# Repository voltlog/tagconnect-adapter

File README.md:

# TagConnect to ST-Link/J-Link JTAG Adapter PCB
I designed this adapter PCB to alow easy connection of the standard TC2030 or TC2050 TagConnect series programming cables to the popular programming/debugging tools like the ST-Link or J-Link which feature a different connector.

Additionally a 6-pin VoltLink connector™ has been added so that a standard TC2030 footprint on a PCB can be used to interface to the VoltLink USB to serial adapter.

If you would like to order one of these adapters ready assembled, check out my [Tindie store](https://voltlog.com/y/tagco).

More info about this project in [Voltlog #460](https://youtu.be/9-e_gcYaEM0).

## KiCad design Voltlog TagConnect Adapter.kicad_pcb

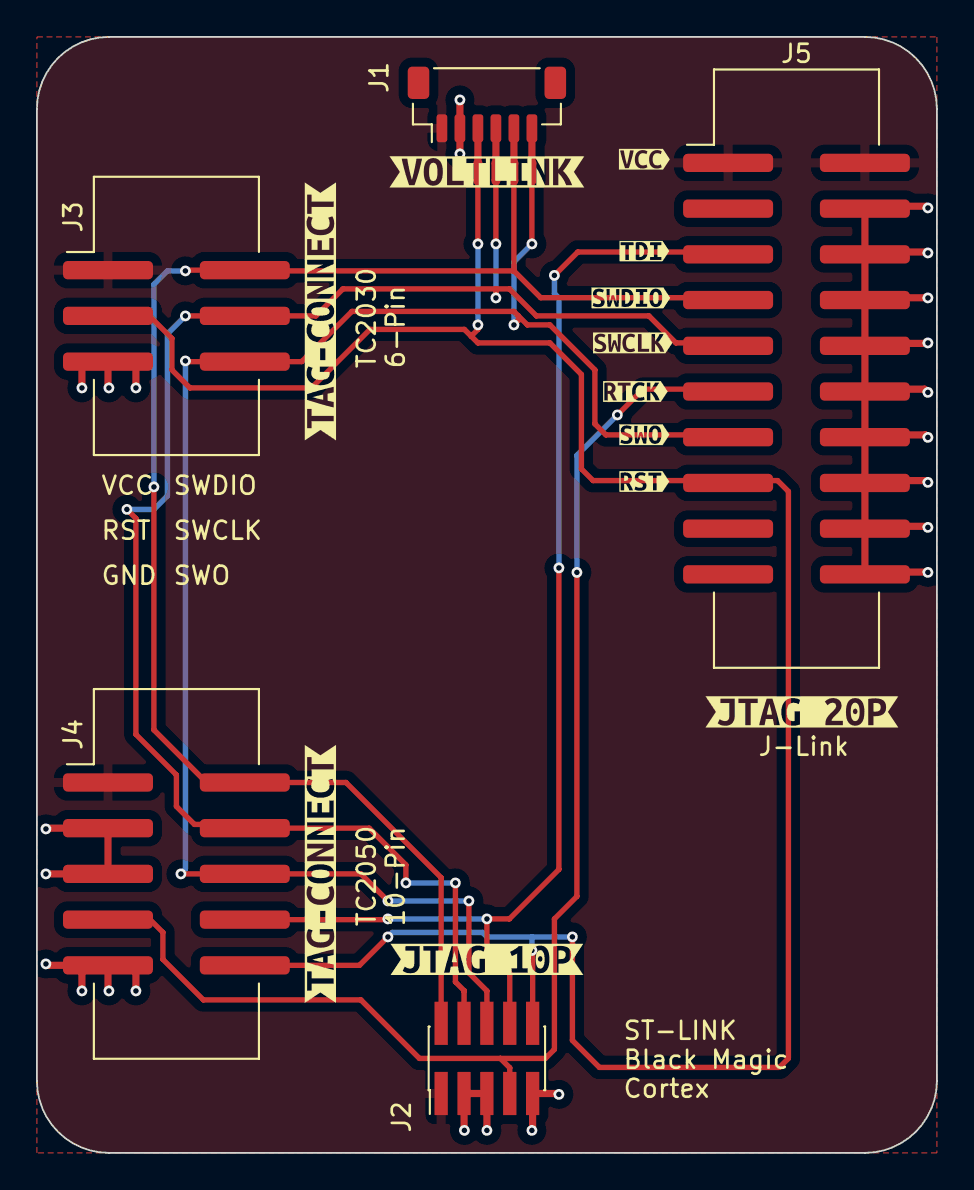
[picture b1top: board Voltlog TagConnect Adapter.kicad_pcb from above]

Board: 2 copper layers, 50.0 x 62.0 mm, 22 parts (0 on the bottom side), 12 nets.

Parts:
J1: VoltLink_target; VoltLink-vertical
J2: JTAG 10pin P1.27mm; PinHeader_2x05_P1.27mm_Vertical_SMD
J3: TC2030-IDC 6-Pin; IDC-Header_2x03_P2.54mm_Vertical_SMD
J4: TC2050-IDC 10-Pin; IDC-Header_2x05_P2.54mm_Vertical_SMD
J5: Conn_ARM_JTAG_SWD_20; IDC-Header_2x10_P2.54mm_Vertical_SMD
NT1, NT2, NT3, NT4: NetTie_2; NetTie-2_SMD_Pad0.5mm
V1: VOLTLOG_LOGO; voltlog_mask_3mm
kibuzzard-64FC233E: G***; kibuzzard-64FC233E
kibuzzard-64FC234D: G***; kibuzzard-64FC234D
kibuzzard-64FC235A: G***; kibuzzard-64FC235A
kibuzzard-64FC2381: G***; kibuzzard-64FC2381
kibuzzard-64FC2395: G***; kibuzzard-64FC2395
kibuzzard-6507D7D7: G***; kibuzzard-6507D7D7
kibuzzard-6507D7E8: G***; kibuzzard-6507D7E8
kibuzzard-6507D7FA: G***; kibuzzard-6507D7FA
kibuzzard-6507D800: G***; kibuzzard-6507D800
kibuzzard-6507D807: G***; kibuzzard-6507D807
kibuzzard-6507D812: G***; kibuzzard-6507D812
kibuzzard-6507D818: G***; kibuzzard-6507D818

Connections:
/EN: J1.6 (EN), NT4.1
/IO0: J1.5 (IO0), NT3.1
/RESET: J2.10, J3.3, J4.10, J5.15 (~SRST), NT1.2
/RTCK: J2.7, J4.7, J5.11 (RTCK)
/RXD: J1.4 (RXD), NT2.1
/TCLK/SWCLK: J2.4, J3.4, J4.4, J5.9 (TCK/SWDCLK), NT2.2
/TDI: J2.8, J4.8, J5.5 (TDI)
/TDO/SWO: J2.6, J3.6, J4.6, J5.13 (TDO/SWO), NT4.2
/TMS/SWDIO: J2.2, J3.2, J4.2, J5.7 (TMS/SWDIO), NT3.2
/TXD: J1.3 (TXD), NT1.1
GND: J1.2 (GND), J2.3, J2.5, J2.9, J3.5, J4.3, J4.5, J4.9, J5.4 (GND), J5.6 (GND), J5.8 (GND), J5.10 (GND), J5.12 (GND), J5.14 (GND), J5.16 (GND), J5.18 (GND), J5.20 (GND)
VCC: J1.1 (3V3), J2.1, J3.1, J4.1, J5.1 (VTREF), J5.2 (VCC/NC)

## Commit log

2023-10-24 Initial commit revA
2023-10-24 Added assembled pcb img
